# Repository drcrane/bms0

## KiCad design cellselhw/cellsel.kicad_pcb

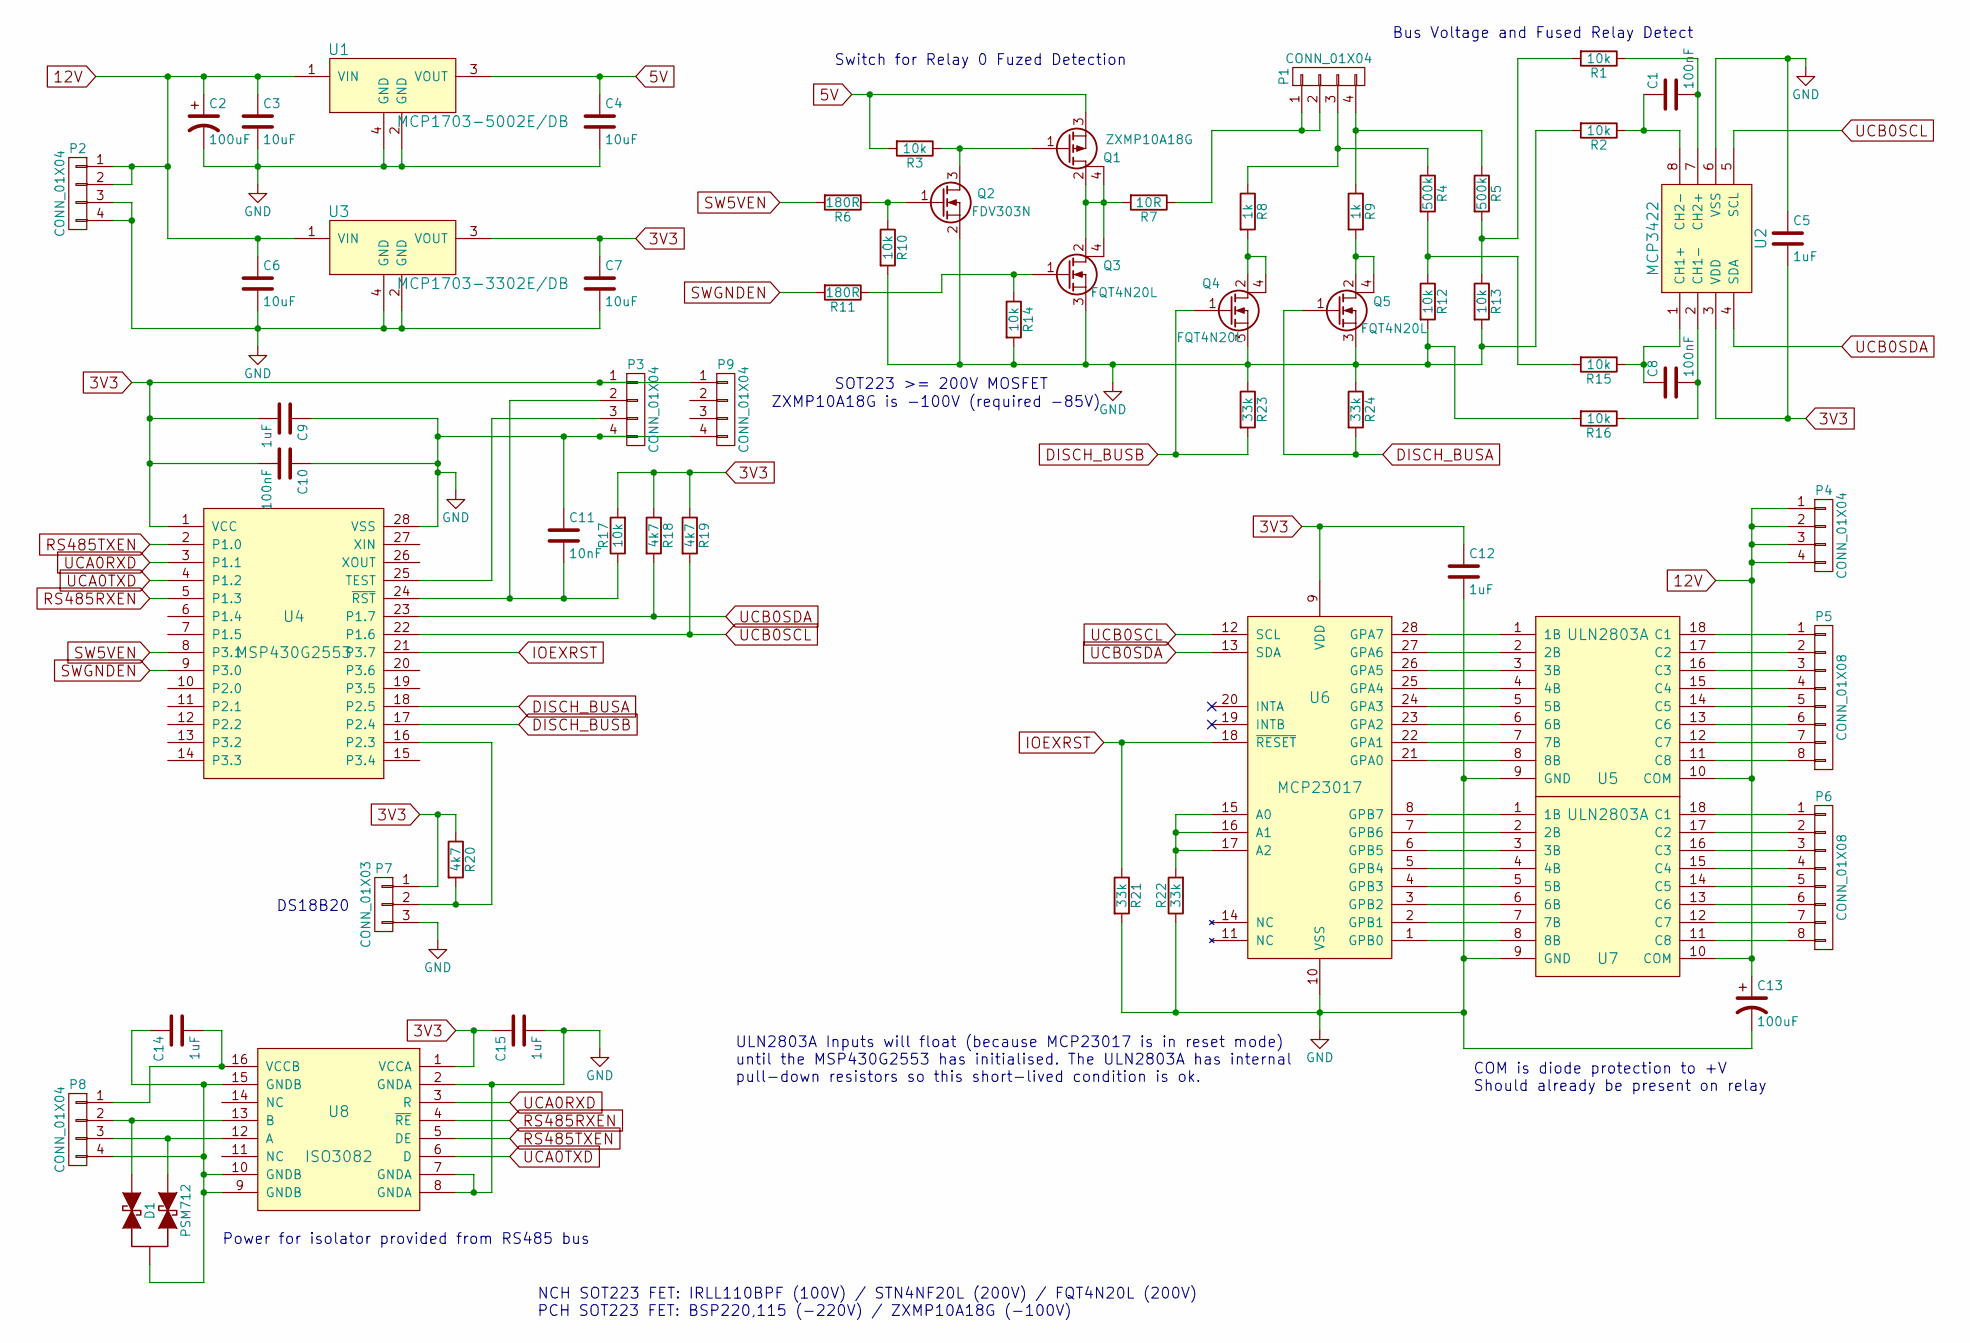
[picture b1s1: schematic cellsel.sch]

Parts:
C1, C8, C10: 100nF; C_0603
C2: 100uF; C_1210
C3, C4, C6, C7: 10uF; C_1206
C5, C9, C12, C14, C15: 1uF; C_0805
C11: 10nF; C_0603
C13: 100uF; C_1206
D1: PSM712; SOT-23
P1, P2, P4, P8, P9: CONN_01X04; Molex_KK-6410-04_04x2.54mm_Straight
P3: CONN_01X04; MINICON_01X04
P5, P6: CONN_01X08; Molex_KK-6410-08_08x2.54mm_Straight
P7: CONN_01X03; DS18B20
Q1: ZXMP10A18G; SOT-223
Q2: FDV303N; SOT-23
Q3, Q4, Q5: FQT4N20L; SOT-223
R1, R2, R3, R10, R14, R15, R16, R17: 10k; R_0603
R4, R5: 500k; PRECISION_RESISTOR_5MM
R6, R11: 180R; R_0603
R7: 10R; R_0805
R8, R9: 1k; R_0805
R12, R13: 10k; PRECISION_RESISTOR_5MM
R18, R19, R20: 4k7; R_0603
R21, R22, R23, R24: 33k; R_0603
U1: MCP1703-5002E/DB; SOT-223
U2: MCP3422; SOIC-8_3.9x4.9mm_Pitch1.27mm
U3: MCP1703-3302E/DB; SOT-223
U4: MSP430G2553; TSSOP-28_4.4x9.7mm_Pitch0.65mm
U5, U7: ULN2803A; DIP-18_W7.62mm
U6: MCP23017; SOIC-28W_7.5x17.9mm_Pitch1.27mm
U8: ISO3082; SOIC-16W_7.5x10.3mm_Pitch1.27mm

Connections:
3V3: C5.2, C7.1, C9.2, C10.2, C12.1, C15.1, P3.1, P7.1, P9.1, R17.2, R18.1, R19.1, R20.1, U2.3 (VDD), U3.3 (VOUT), U4.1 (VCC), U6.9 (VDD), U8.1 (VCCA)
5V: C4.1, Q1.3 (S), R3.2, U1.3 (VOUT)
12V: C2.1, C3.1, C6.1, C13.1, P2.1, P2.2, P4.1, P4.2, P4.3, P4.4, U1.1 (VIN), U3.1 (VIN), U5.10 (COM), U7.10 (COM)
DISCH_BUSA: Q5.1 (G), R24.2, U4.18 (P2.5)
DISCH_BUSB: Q4.1 (G), R23.2, U4.17 (P2.4)
GND: C2.2, C3.2, C4.2, C5.1, C6.2, C7.2, C9.1, C10.1, C11.1, C12.2, C13.2, C15.2, P2.3, P2.4, P3.4, P7.3, P9.4, Q2.2 (S), Q3.3 (S), Q4.3 (S), Q5.3 (S), R2.2, R10.2, R12.2, R13.2, R14.2, R16.2, R21.2, R22.1, R23.1, R24.1, U1.2 (GND), U1.4 (GND), U2.6 (VSS), U3.2 (GND), U3.4 (GND), U4.28 (VSS), U5.9 (GND), U6.10 (VSS), U7.9 (GND), U8.2 (GNDA), U8.7 (GNDA), U8.8 (GNDA)
IOEXRST: R21.1, U4.21 (P3.7), U6.18 (~RESET)
unnamed: C1.1, R2.1, U2.8 (CH2-)
unnamed: C1.2, R1.1, U2.7 (CH2+)
unnamed: C8.1, R15.1, U2.1 (CH1+)
unnamed: C8.2, R16.1, U2.2 (CH1-)
unnamed: C11.2, P3.2, R17.1, U4.24 (~RST)
unnamed: C14.1, D1.3, P8.4, U8.9 (GNDB), U8.10 (GNDB), U8.15 (GNDB)
unnamed: C14.2, P8.1, U8.16 (VCCB)
unnamed: D1.1, P8.2, U8.13 (B)
unnamed: D1.2, P8.3, U8.12 (A)
unnamed: P1.1, P1.2, R7.1
unnamed: P1.3, R4.1, R8.1
unnamed: P1.4, R5.1, R9.1
unnamed: P3.3, U4.25 (TEST)
unnamed: P5.1, U5.18 (C1)
unnamed: P5.2, U5.17 (C2)
unnamed: P5.3, U5.16 (C3)
unnamed: P5.4, U5.15 (C4)
unnamed: P5.5, U5.14 (C5)
unnamed: P5.6, U5.13 (C6)
unnamed: P5.7, U5.12 (C7)
unnamed: P5.8, U5.11 (C8)
unnamed: P6.1, U7.18 (C1)
unnamed: P6.2, U7.17 (C2)
unnamed: P6.3, U7.16 (C3)
unnamed: P6.4, U7.15 (C4)
unnamed: P6.5, U7.14 (C5)
unnamed: P6.6, U7.13 (C6)
unnamed: P6.7, U7.12 (C7)
unnamed: P6.8, U7.11 (C8)
unnamed: P7.2, R20.2, U4.16 (P2.3)
unnamed: Q1.1 (G), Q2.3 (D), R3.1
unnamed: Q1.2 (D), Q1.4 (D), Q3.2 (D), Q3.4 (D), R7.2
unnamed: Q2.1 (G), R6.1, R10.1
unnamed: Q3.1 (G), R11.1, R14.1
unnamed: Q4.2 (D), Q4.4 (D), R8.2
unnamed: Q5.2 (D), Q5.4 (D), R9.2
unnamed: R1.2, R5.2, R13.1
unnamed: R4.2, R12.1, R15.2
unnamed: R22.2, U6.15 (A0), U6.16 (A1), U6.17 (A2)
unnamed: U5.1 (1B), U6.28 (GPA7)
unnamed: U5.2 (2B), U6.27 (GPA6)
unnamed: U5.3 (3B), U6.26 (GPA5)
unnamed: U5.4 (4B), U6.25 (GPA4)
unnamed: U5.5 (5B), U6.24 (GPA3)
unnamed: U5.6 (6B), U6.23 (GPA2)
unnamed: U5.7 (7B), U6.22 (GPA1)
unnamed: U5.8 (8B), U6.21 (GPA0)
unnamed: U6.1 (GPB0), U7.8 (8B)
unnamed: U6.2 (GPB1), U7.7 (7B)
unnamed: U6.3 (GPB2), U7.6 (6B)
unnamed: U6.4 (GPB3), U7.5 (5B)
unnamed: U6.5 (GPB4), U7.4 (4B)
unnamed: U6.6 (GPB5), U7.3 (3B)
unnamed: U6.7 (GPB6), U7.2 (2B)
unnamed: U6.8 (GPB7), U7.1 (1B)
RS485RXEN: U4.5 (P1.3), U8.4 (~RE)
RS485TXEN: U4.2 (P1.0), U8.5 (DE)
SW5VEN: R6.2, U4.8 (P3.1)
SWGNDEN: R11.2, U4.9 (P3.0)
UCA0RXD: U4.3 (P1.1), U8.3 (R)
UCA0TXD: U4.4 (P1.2), U8.6 (D)
UCB0SCL: R19.2, U2.5 (SCL), U4.22 (P1.6), U6.12 (SCL)
UCB0SDA: R18.2, U2.4 (SDA), U4.23 (P1.7), U6.13 (SDA)

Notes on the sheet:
Switch for Relay 0 Fuzed Detection
Bus Voltage and Fused Relay Detect
Power for isolator provided from RS485 bus
COM is diode protection to +V Should already be present on relay
SOT223 >= 200V MOSFET
NCH SOT223 FET: IRLL110BPF (100V) / STN4NF20L (200V) / FQT4N20L (200V) PCH SOT223 FET: BSP220,115 (-220V) / ZXMP10A18G (-100V)
DS18B20
ZXMP10A18G is -100V (required -85V)
ULN2803A Inputs will float (because MCP23017 is in reset mode) until the MSP430G2553 has initialised. The ULN2803A has internal pull-down resistors so this short-lived condition is ok.

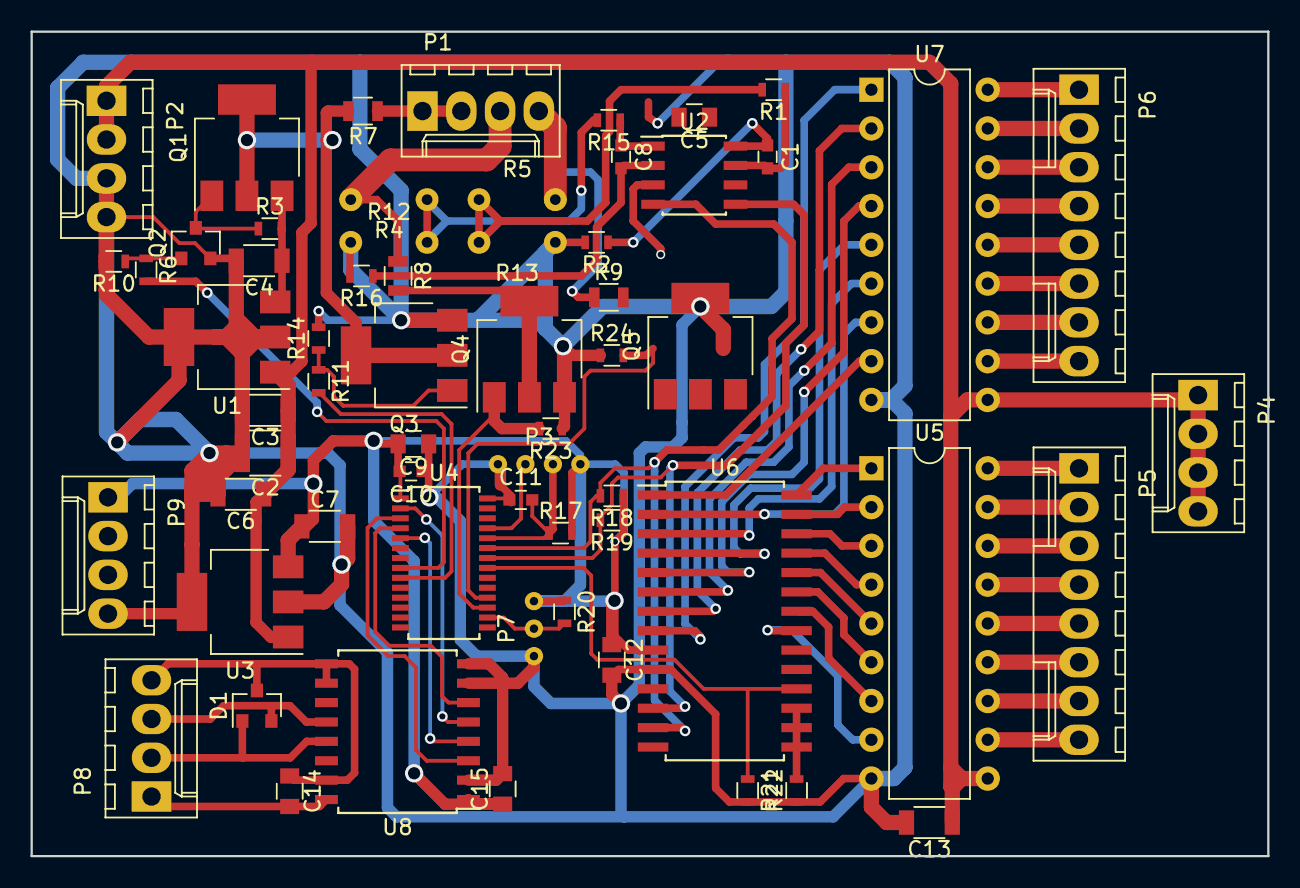
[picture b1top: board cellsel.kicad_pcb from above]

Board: 2 copper layers, 81.0 x 54.0 mm, 62 parts (0 on the bottom side), 70 nets.

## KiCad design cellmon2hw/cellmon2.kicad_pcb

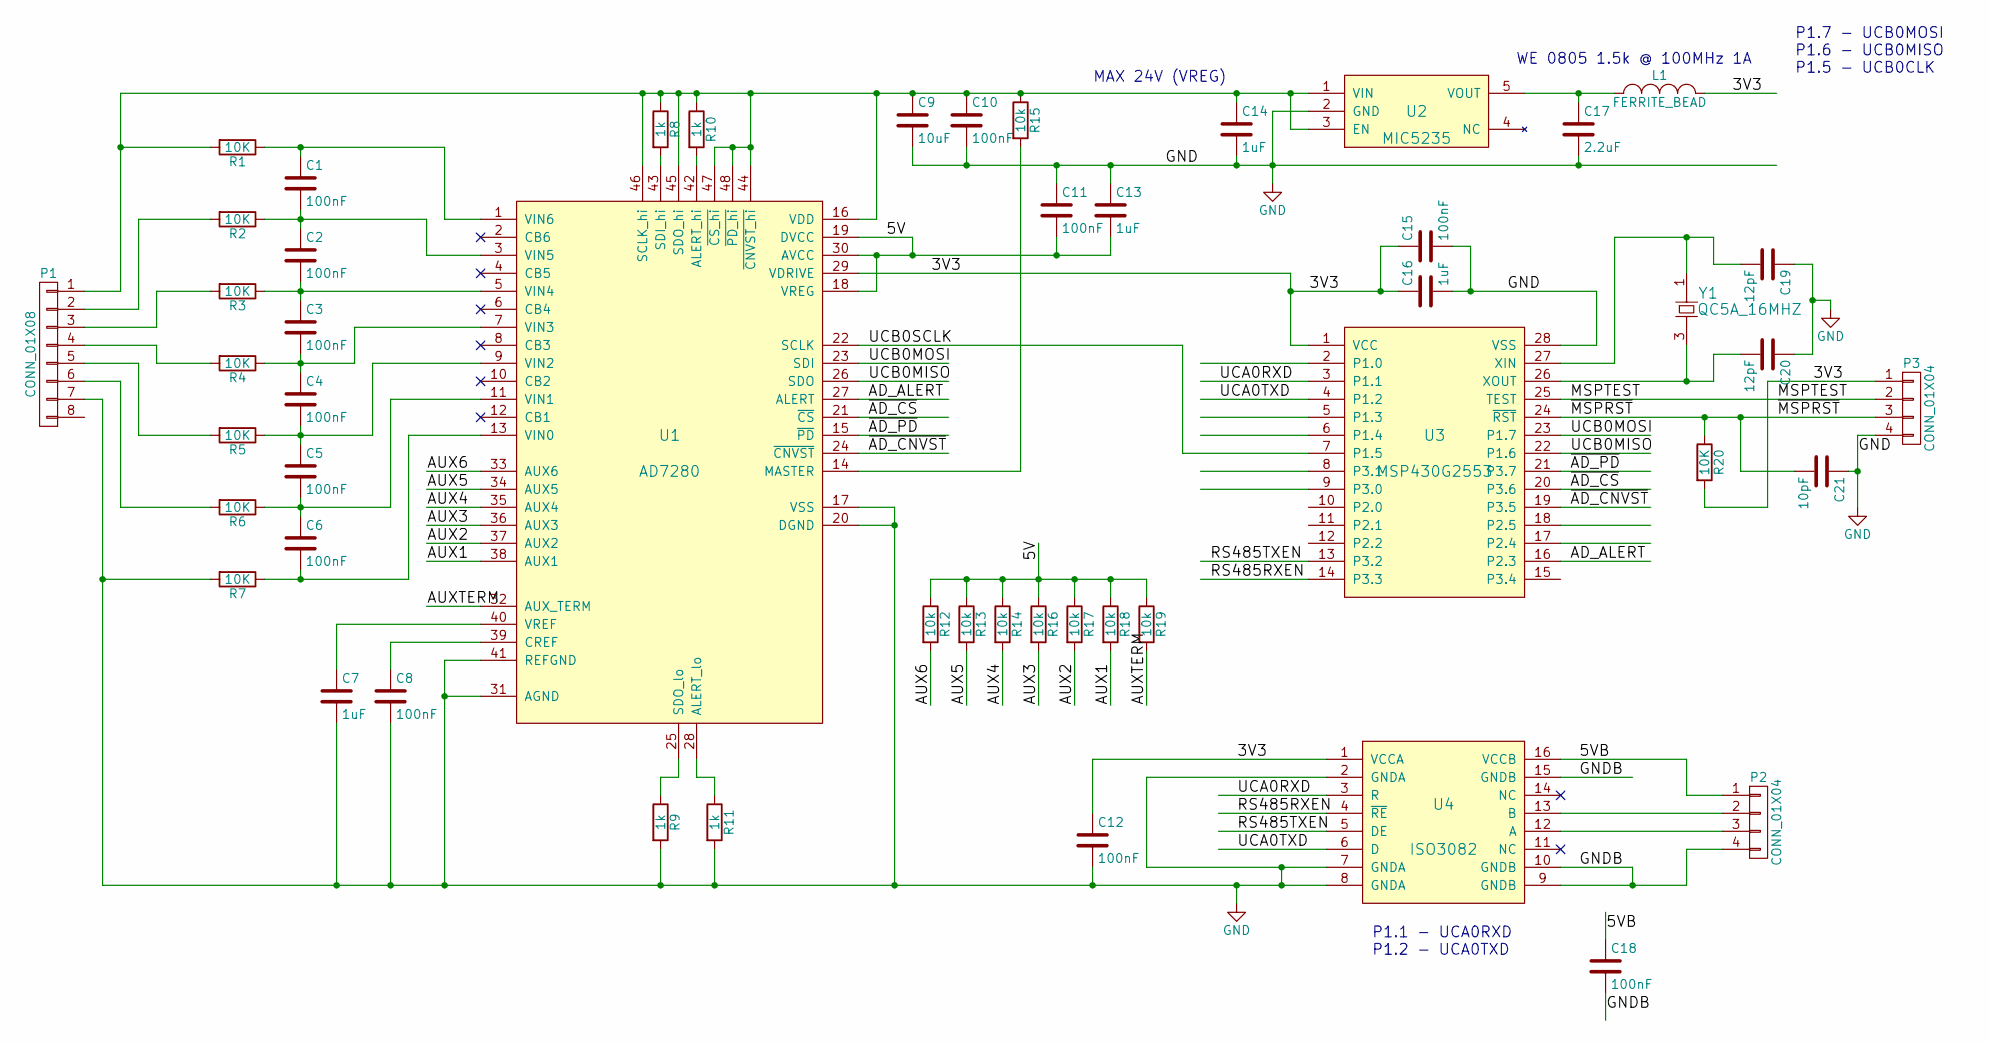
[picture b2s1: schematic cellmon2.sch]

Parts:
C1, C2, C3, C4, C5, C6, C8, C10, C11, C12, C15, C18: 100nF; C_0603
C7, C13, C14, C16: 1uF; C_0805
C9: 10uF; C_1206
C17: 2.2uF; C_0805
C19, C20: 12pF; C_0603
C21: 10pF; C_0603
L1: FERRITE_BEAD; C_0805
P1: CONN_01X08; Molex_KK-6410-08_08x2.54mm_Straight
P2, P3: CONN_01X04; Molex_KK-6410-04_04x2.54mm_Straight
R1, R2, R3, R4, R5, R6, R7, R20: 10K; R_0603
R8, R9, R10, R11: 1k; R_0603
R12, R13, R14, R15, R16, R17, R18, R19: 10k; R_0603
U1: AD7280; LQFP-48_7x7mm_Pitch0.5mm
U2: MIC5235; SOT-23-5
U3: MSP430G2553; TSSOP-28_4.4x9.7mm_Pitch0.65mm
U4: ISO3082; SOIC-16W_7.5x10.3mm_Pitch1.27mm
Y1: QC5A_16MHZ; Crystal_SMD_Abracon_ABM3C-4pin_5.0x3.2mm

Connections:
/3V3: C12.1, C15.1, C16.1, L1.2, P3.1, R20.2, U1.29 (VDRIVE), U3.1 (VCC), U4.1 (VCCA)
/5V: C11.2, C13.2, R12.1, R13.1, R14.1, R16.1, R17.1, R18.1, R19.1, U1.18 (VREG), U1.19 (DVCC), U1.30 (AVCC)
/5VB: C18.1, P2.1, U4.16 (VCCB)
/AD_ALERT: U1.27 (ALERT), U3.16 (P2.3)
/AUX1: R18.2, U1.38 (AUX1)
/AUX2: R17.2, U1.37 (AUX2)
/AUX3: R16.2, U1.36 (AUX3)
/AUX4: R14.2, U1.35 (AUX4)
/AUX5: R13.2, U1.34 (AUX5)
/AUX6: R12.2, U1.33 (AUX6)
/AUXTERM: R19.2, U1.32 (AUX_TERM)
/GNDB: C18.2, P2.4, U4.9 (GNDB), U4.10 (GNDB), U4.15 (GNDB)
/MSPTEST: P3.2, U3.25 (TEST)
/RS485RXEN: U3.14 (P3.3), U4.4 (~RE)
/RS485TXEN: U3.13 (P3.2), U4.5 (DE)
/UCA0RXD: U3.3 (P1.1), U4.3 (R)
/UCA0TXD: U3.4 (P1.2), U4.6 (D)
/UCB0MISO: U1.26 (SDO), U3.22 (P1.6)
/UCB0MOSI: U1.23 (SDI), U3.23 (P1.7)
/UCB0SCLK: U1.22 (SCLK), U3.7 (P1.5)
/~AD_CNVST: U1.24 (~CNVST), U3.19 (P3.5)
/~AD_CS: U1.21 (~CS), U3.20 (P3.6)
/~AD_PD: U1.15 (~PD), U3.21 (P3.7)
/~MSPRST: C21.2, P3.3, R20.1, U3.24 (~RST)
GND: C7.2, C8.2, C9.2, C10.2, C11.1, C12.2, C13.1, C14.2, C15.2, C16.2, C17.2, C19.1, C20.1, C21.1, P1.7, P3.4, R7.2, R9.2, R11.2, U1.17 (VSS), U1.20 (DGND), U1.31 (AGND), U1.41 (REFGND), U2.2 (GND), U3.28 (VSS), U4.2 (GNDA), U4.7 (GNDA), U4.8 (GNDA)
unnamed: C1.1, R1.1, U1.1 (VIN6)
unnamed: C1.2, C2.1, R2.1, U1.3 (VIN5)
unnamed: C2.2, C3.1, R3.1, U1.5 (VIN4)
unnamed: C3.2, C4.1, R4.1, U1.7 (VIN3)
unnamed: C4.2, C5.1, R5.1, U1.9 (VIN2)
unnamed: C5.2, C6.1, R6.1, U1.11 (VIN1)
unnamed: C6.2, R7.1, U1.13 (VIN0)
unnamed: C7.1, U1.40 (VREF)
unnamed: C8.1, U1.39 (CREF)
unnamed: C9.1, C10.1, C14.1, P1.1, R1.2, R8.1, R10.1, R15.1, U1.16 (VDD), U1.44 (~CNVST_hi), U1.45 (SDO_hi), U1.46 (SCLK_hi), U1.47 (~CS_hi), U1.48 (~PD_hi), U2.1 (VIN), U2.3 (EN)
unnamed: C17.1, L1.1, U2.5 (VOUT)
unnamed: C19.2, U3.27 (XIN), Y1.1
unnamed: C20.2, U3.26 (XOUT), Y1.3
unnamed: P1.2, R2.2
unnamed: P1.3, R3.2
unnamed: P1.4, R4.2
unnamed: P1.5, R5.2
unnamed: P1.6, R6.2
unnamed: P2.2, U4.13 (B)
unnamed: P2.3, U4.12 (A)
unnamed: R8.2, U1.43 (SDI_hi)
unnamed: R9.1, U1.25 (SDO_lo)
unnamed: R10.2, U1.42 (ALERT_hi)
unnamed: R11.1, U1.28 (ALERT_lo)
unnamed: R15.2, U1.14 (MASTER)

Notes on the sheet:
P1.7 - UCB0MOSI P1.6 - UCB0MISO P1.5 - UCB0CLK
P1.1 - UCA0RXD P1.2 - UCA0TXD
MAX 24V (VREG)
WE 0805 1.5k @ 100MHz 1A

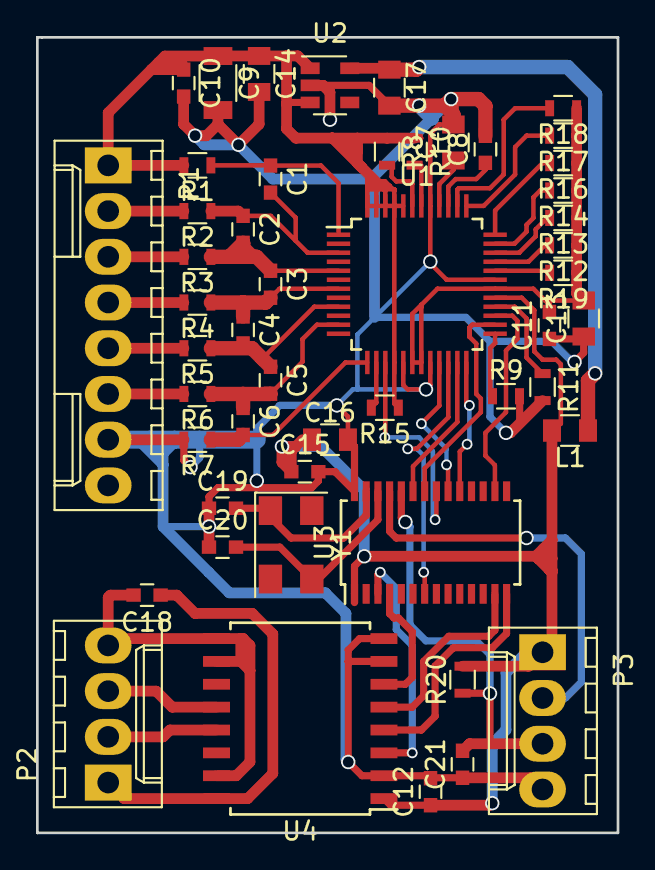
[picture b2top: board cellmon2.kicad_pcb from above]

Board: 2 copper layers, 32.3 x 44.2 mm, 50 parts (0 on the bottom side), 50 nets.

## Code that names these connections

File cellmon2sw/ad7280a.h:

#ifndef __AD7280A_H
#define __AD7280A_H

#include <stdint.h>

#define AD_PORT  P3OUT
#define AD_CS    BIT6
#define AD_CNVST BIT5
#define AD_PD    BIT7

uint16_t ad7280a_decodevoltage(uint8_t * ptr);
void ad7280a_rw(uint8_t * buf, uint8_t dev, uint8_t reg, uint8_t val, uint8_t write_all);
//uint32_t ad7280a_write(uint8_t dev, uint8_t reg, uint8_t val, uint8_t write_all);

#endif // __AD7280A_H

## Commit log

2018-02-03 Added Makefile for cellmon2sw
2018-02-08 Added bus discharge transistors
2018-02-10 Schematic Complete
2018-02-11 PCB Layout Stage 1
2018-03-10 Finalused Transistor Selection
2018-03-10 PCB RC1 Ready
2018-03-11 Final Production Ready Prototype
2018-03-15 Minor last-minute refinements
2018-03-31 Connected Power Incorrectly on ADC
2019-06-30 RS485 Packet Interface Added
2019-07-06 Read from AD7280 Working when send correct packet
2019-07-07 Working CRC Check and Voltage Decode
2019-07-07 Cell Selector Added, RS485_IF working.
2019-07-18 Extended the i2c Relay Fused Checker
